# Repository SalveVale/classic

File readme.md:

# classic

*A short description of the keyboard/project*

* Keyboard Maintainer: [Ben Powell](https://github.com/Ben Powell)
* Hardware Supported: *The PCBs, controllers supported*
* Hardware Availability: *Links to where you can find this hardware*

Make example for this keyboard (after setting up your build environment):

    make classic:default

Flashing example for this keyboard:

    make classic:default:flash

See the [build environment setup](https://docs.qmk.fm/#/getting_started_build_tools) and the [make instructions](https://docs.qmk.fm/#/getting_started_make_guide) for more information. Brand new to QMK? Start with our [Complete Newbs Guide](https://docs.qmk.fm/#/newbs).

## Bootloader

Enter the bootloader in 3 ways:

* **Bootmagic reset**: Hold down the key at (0,0) in the matrix (usually the top left key or Escape) and plug in the keyboard
* **Physical reset button**: Briefly press the button on the back of the PCB - some may have pads you must short instead
* **Keycode in layout**: Press the key mapped to `QK_BOOT` if it is available

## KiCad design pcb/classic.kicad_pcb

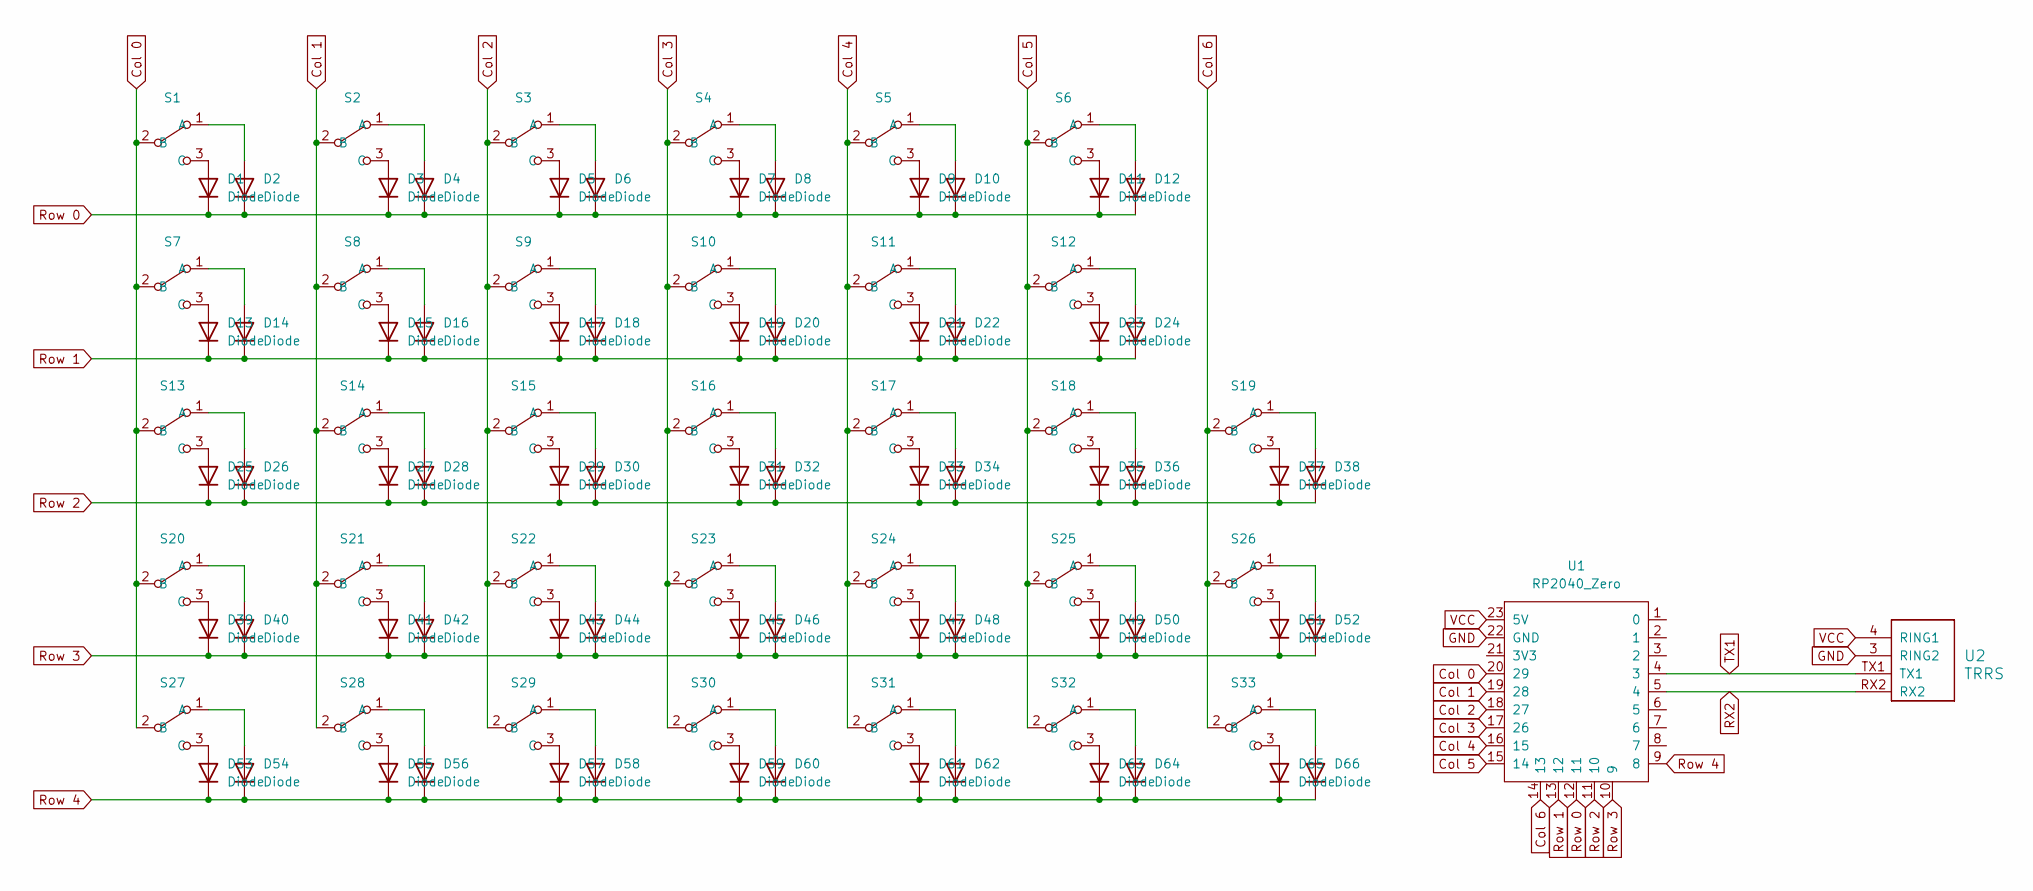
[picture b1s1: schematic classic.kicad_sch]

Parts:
D1, D2, D3, D4, D5, D6, D7, D8, D9, D10, D11, D12, D13, D14, D15, D16, D17, D18, D19, D20, D21, D22, D23, D24, D25, D26, D27, D28, D29, D30, D31, D32, D33, D34, D35, D36, D37, D38, D39, D40, D41, D42, D43, D44, D45, D46, D47, D48, D49, D50, D51, D52, D53, D54, D55, D56, D57, D58, D59, D60, D61, D62, D63, D64, D65, D66: Diode; Diode_SOD-123_clean
S1, S2, S3, S4, S5, S6, S7, S8, S9, S10, S11, S12, S13, S14, S15, S16, S17, S18, S19, S20, S21, S22, S23, S24, S25, S26, S27, S28, S29, S30, S31, S32, S33: SW_choc_v1_HS_1u_Reversible_clean
U1: RP2040_Zero
U2: TRRS; TRRS-lily58

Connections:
Col 0: S1.2 (B), S7.2 (B), S13.2 (B), S20.2 (B), S27.2 (B), U1.20 (29)
Col 1: S2.2 (B), S8.2 (B), S14.2 (B), S21.2 (B), S28.2 (B), U1.19 (28)
Col 2: S3.2 (B), S9.2 (B), S15.2 (B), S22.2 (B), S29.2 (B), U1.18 (27)
Col 3: S4.2 (B), S10.2 (B), S16.2 (B), S23.2 (B), S30.2 (B), U1.17 (26)
Col 4: S5.2 (B), S11.2 (B), S17.2 (B), S24.2 (B), S31.2 (B), U1.16 (15)
Col 5: S6.2 (B), S12.2 (B), S18.2 (B), S25.2 (B), S32.2 (B), U1.15 (14)
Col 6: S19.2 (B), S26.2 (B), S33.2 (B), U1.14 (13)
GND: U1.22 (GND), U2.3 (RING2)
unnamed: D1.2 (A), S1.3 (C)
unnamed: D2.2 (A), S1.1 (A)
unnamed: D3.2 (A), S2.3 (C)
unnamed: D4.2 (A), S2.1 (A)
unnamed: D5.2 (A), S3.3 (C)
unnamed: D6.2 (A), S3.1 (A)
unnamed: D7.2 (A), S4.3 (C)
unnamed: D8.2 (A), S4.1 (A)
unnamed: D9.2 (A), S5.3 (C)
unnamed: D10.2 (A), S5.1 (A)
unnamed: D11.2 (A), S6.3 (C)
unnamed: D12.2 (A), S6.1 (A)
unnamed: D13.2 (A), S7.3 (C)
unnamed: D14.2 (A), S7.1 (A)
unnamed: D15.2 (A), S8.3 (C)
unnamed: D16.2 (A), S8.1 (A)
unnamed: D17.2 (A), S9.3 (C)
unnamed: D18.2 (A), S9.1 (A)
unnamed: D19.2 (A), S10.3 (C)
unnamed: D20.2 (A), S10.1 (A)
unnamed: D21.2 (A), S11.3 (C)
unnamed: D22.2 (A), S11.1 (A)
unnamed: D23.2 (A), S12.3 (C)
unnamed: D24.2 (A), S12.1 (A)
unnamed: D25.2 (A), S13.3 (C)
unnamed: D26.2 (A), S13.1 (A)
unnamed: D27.2 (A), S14.3 (C)
unnamed: D28.2 (A), S14.1 (A)
unnamed: D29.2 (A), S15.3 (C)
unnamed: D30.2 (A), S15.1 (A)
unnamed: D31.2 (A), S16.3 (C)
unnamed: D32.2 (A), S16.1 (A)
unnamed: D33.2 (A), S17.3 (C)
unnamed: D34.2 (A), S17.1 (A)
unnamed: D35.2 (A), S18.3 (C)
unnamed: D36.2 (A), S18.1 (A)
unnamed: D37.2 (A), S19.3 (C)
unnamed: D38.2 (A), S19.1 (A)
unnamed: D39.2 (A), S20.3 (C)
unnamed: D40.2 (A), S20.1 (A)
unnamed: D41.2 (A), S21.3 (C)
unnamed: D42.2 (A), S21.1 (A)
unnamed: D43.2 (A), S22.3 (C)
unnamed: D44.2 (A), S22.1 (A)
unnamed: D45.2 (A), S23.3 (C)
unnamed: D46.2 (A), S23.1 (A)
unnamed: D47.2 (A), S24.3 (C)
unnamed: D48.2 (A), S24.1 (A)
unnamed: D49.2 (A), S25.3 (C)
unnamed: D50.2 (A), S25.1 (A)
unnamed: D51.2 (A), S26.3 (C)
unnamed: D52.2 (A), S26.1 (A)
unnamed: D53.2 (A), S27.3 (C)
unnamed: D54.2 (A), S27.1 (A)
unnamed: D55.2 (A), S28.3 (C)
unnamed: D56.2 (A), S28.1 (A)
unnamed: D57.2 (A), S29.3 (C)
unnamed: D58.2 (A), S29.1 (A)
unnamed: D59.2 (A), S30.3 (C)
unnamed: D60.2 (A), S30.1 (A)
unnamed: D61.2 (A), S31.3 (C)
unnamed: D62.2 (A), S31.1 (A)
unnamed: D63.2 (A), S32.3 (C)
unnamed: D64.2 (A), S32.1 (A)
unnamed: D65.2 (A), S33.3 (C)
unnamed: D66.2 (A), S33.1 (A)
RX2: U1.5 (4), U2.RX2
Row 0: D1.1 (K), D2.1 (K), D3.1 (K), D4.1 (K), D5.1 (K), D6.1 (K), D7.1 (K), D8.1 (K), D9.1 (K), D10.1 (K), D11.1 (K), D12.1 (K), U1.12 (11)
Row 1: D13.1 (K), D14.1 (K), D15.1 (K), D16.1 (K), D17.1 (K), D18.1 (K), D19.1 (K), D20.1 (K), D21.1 (K), D22.1 (K), D23.1 (K), D24.1 (K), U1.13 (12)
Row 2: D25.1 (K), D26.1 (K), D27.1 (K), D28.1 (K), D29.1 (K), D30.1 (K), D31.1 (K), D32.1 (K), D33.1 (K), D34.1 (K), D35.1 (K), D36.1 (K), D37.1 (K), D38.1 (K), U1.11 (10)
Row 3: D39.1 (K), D40.1 (K), D41.1 (K), D42.1 (K), D43.1 (K), D44.1 (K), D45.1 (K), D46.1 (K), D47.1 (K), D48.1 (K), D49.1 (K), D50.1 (K), D51.1 (K), D52.1 (K), U1.10 (9)
Row 4: D53.1 (K), D54.1 (K), D55.1 (K), D56.1 (K), D57.1 (K), D58.1 (K), D59.1 (K), D60.1 (K), D61.1 (K), D62.1 (K), D63.1 (K), D64.1 (K), D65.1 (K), D66.1 (K), U1.9 (8)
TX1: U1.4 (3), U2.TX1
VCC: U1.23 (5V), U2.4 (RING1)

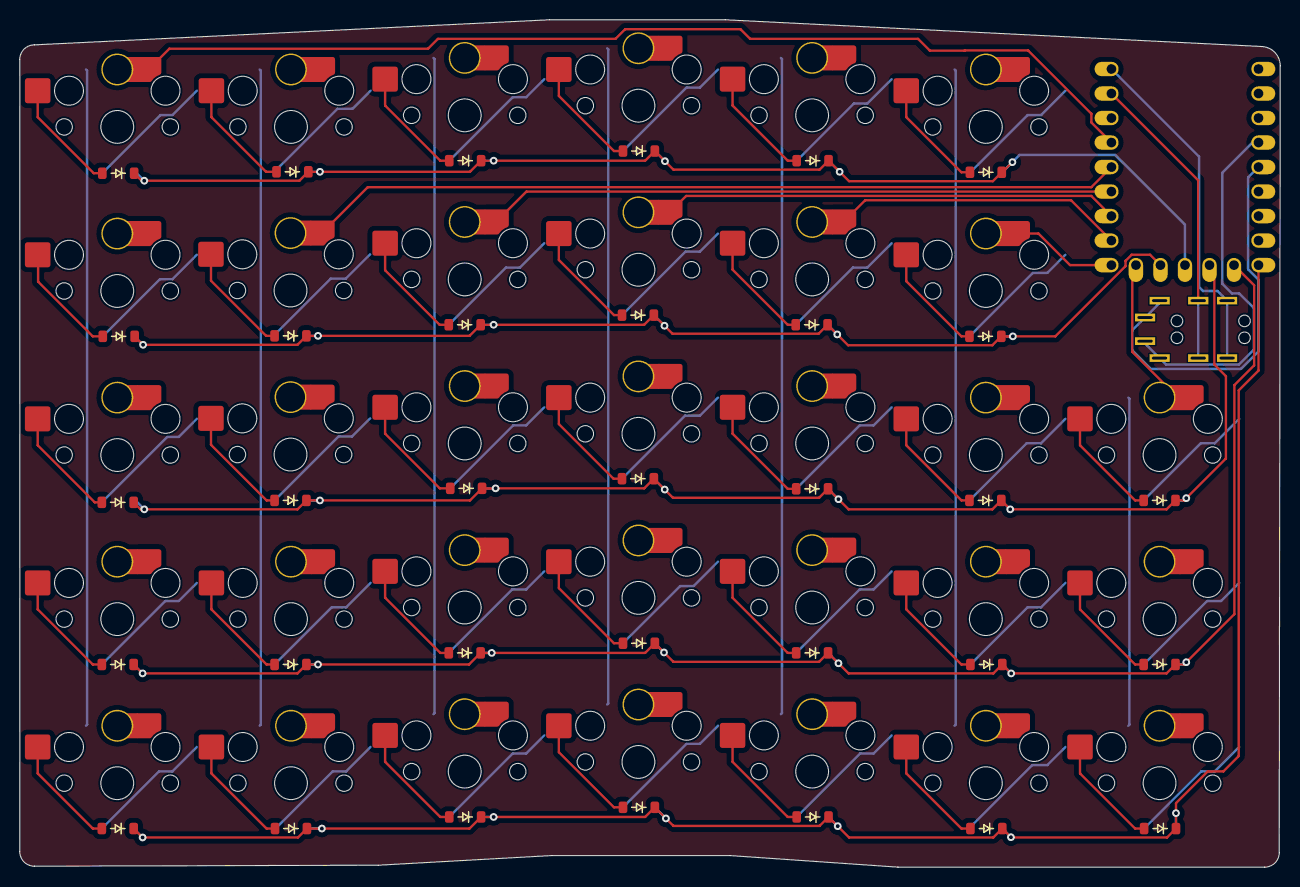
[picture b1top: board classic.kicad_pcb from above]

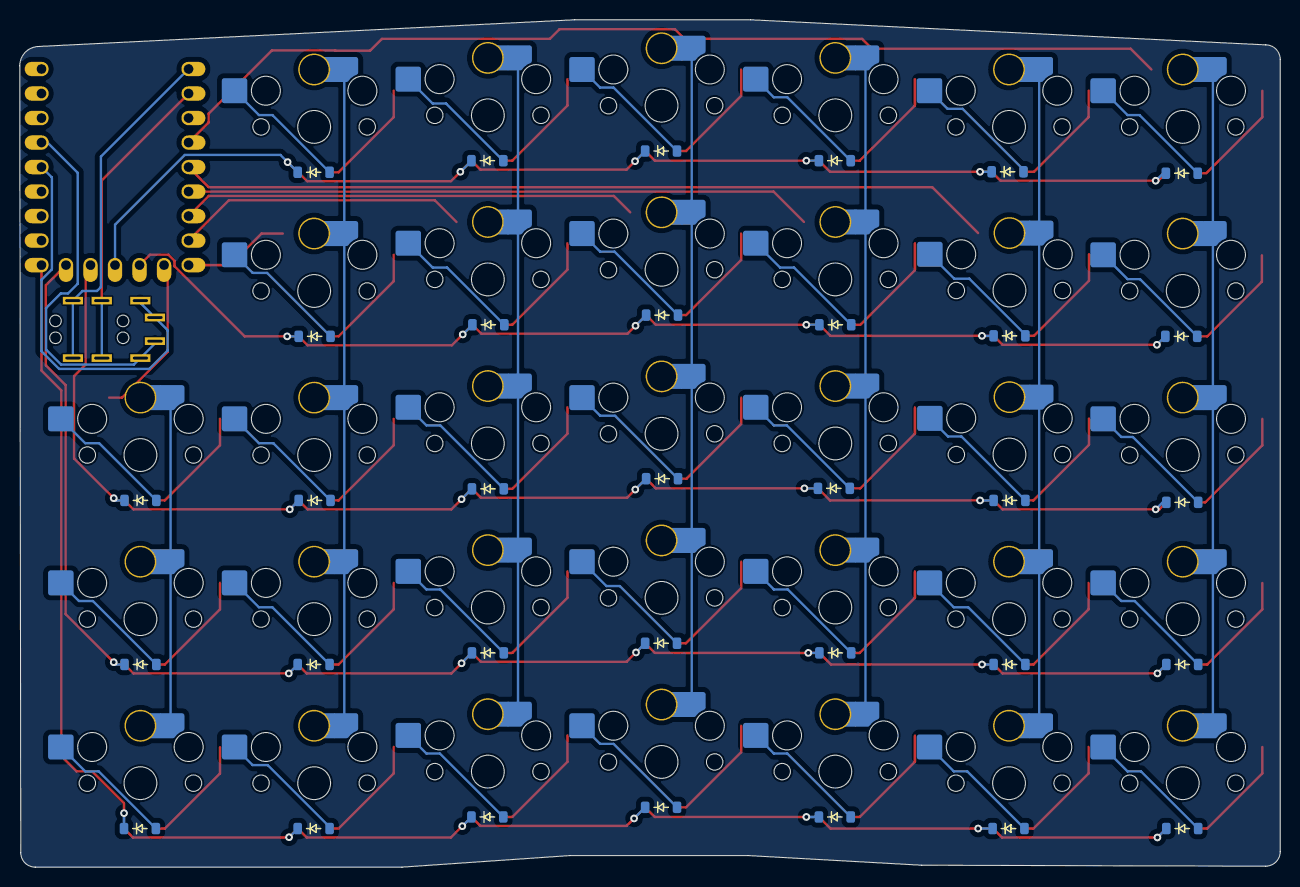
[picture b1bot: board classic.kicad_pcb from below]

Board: 2 copper layers, 130.6 x 87.8 mm, 101 parts (33 on the bottom side), 82 nets.

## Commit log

2024-05-23 Left half sending double keycodes
2024-05-23 Add pcb files
2024-05-23 Fix double keypress issue
2024-05-24 Fixed keycodes in wrong locations
